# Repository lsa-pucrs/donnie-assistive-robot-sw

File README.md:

<!---
[//]: # incluir travis
[//]: #| Linux                           |
[//]: #|---------------------------------|
[//]: #| [![Build Status][master]][repo] |
[//]: # https://github.com/forexample/package-example/blob/master/CMakeLists.txt

[//]: #[master]: https://travis-ci.org/forexample/package-example.svg?branch=master
[//]: #[repo]: https://travis-ci.org/forexample/package-example
-->

# Donnie Software Stack

Robotics has been used to teach young students the basics of programming. However,
most of the programming environments for kids are high visual, based on grab and drag blocks.
**Blind students or students with some visual disability cannot use these teaching resources**.

Donnie project proposes an inclusive robotic programming environment where all students
(with or without visual disabilities) can use.

Donnie comes with two usage options: simulated robot and physical robot. It is recommended to start with the simulated since it does not require building the robot. Moreover, currently the physical robot is functional, but it is still under test.

Currently Donnie is working fine in Linux Operating System, it is not working on Windows Operating Sytem neither in MacOS.

Contents
--------

1. [Features](#features)
2. [Getting Started with the Simulated Donnie Robot](#getting-started-with-the-simulated-donnie-robot)
3. [Building Your Donnie Robot](#building-your-donnie-robot)
4. [Contributors](#contributors)
5. [Contributing](#contributing)
6. [Support](#support)
7. [Papers](#papers)

# Features
---------------

* Robot programming environment for young students with or without visual impairment;
* Assistive programming language called GoDonnie. GoDonnie is TTS and screen reader friendly;
* Integration with a Arduino-based robot with Player robotic middleware;
* Extension of Stage simulator to generate sound clues while the robot is moving;
* Software developed for the simulated robot is compatible with the real Donnie robot;

# Getting Started with the Simulated Donnie Robot
---------------

<!---
TODO colocar um link do Donnie no youtube

-->

 <!--The simulation is recommended if you want to known about Donnie but you dont have the required resources to build your own Donnie robot.-->

 <!--Download this [VM](http://www.osboxes.org/linux-mint/), select the Linux Mint 17.3 'Rosa', and selected the [Mate](https://drive.google.com/file/d/0B_HAFnYs6Ur-NGFCZWNFV2dBN2M/view?usp=sharing) version. Finally, follow the instructions to install Donnie package.
 -->

## Operating System Requirement
 --------
 1. Currently this project requires Ubuntu 16.04.
 [**Ubuntu 16.04**](http://releases.ubuntu.com/16.04/) (Xenial Xerus) is the recommended OS distribution.
 For older computers or VMs, [Lubuntu 16.04](http://cdimage.ubuntu.com/lubuntu/releases/16.04/release/) or [Ubuntu Mate 16.04](https://ubuntu-mate.org/trusty/) are recommended.
 
<!-- * It is recommended to update your packages before the instalation:
> sudo apt-get update
* To install, you can double-click it or execute:
> sudo dpkg -i donnie-player-stage_0.1_amd64.deb
* In case of missing dependencies, try: 
> sudo apt-get -f install
* To unistall:
> sudo dpkg -r donnie-player-stage -->

## Compile and Install Donnie Software on a Desktop Computer

1.Open a terminal, and execute the following commands:

	mkdir ~/donnie; cd ~/donnie
	git clone --recurse-submodules -b devel https://github.com/lsa-pucrs/donnie-assistive-robot-sw.git
	cd donnie-assistive-robot-sw
	chmod +x ./install.sh
	export DONNIE_PATH=/opt/donnie 
	./install.sh
	
2. After the execution of the last command  above, if the installation finished successfully you are ready to go! 
note:The last command above, in general, requires a lot of time to finish.

### Configuring Donnie

The installation scripts make a standard instalation we believe is the most appropriated for the average user.
However, advanced parameters can be set if the user has experience with the appropriate tools.

The build system is based on CMake, so it is required to have some experience with Linux, Make, and CMake.
Every part of Donnie Software Stack is also based on CMake. These are the software parts that can be customized:

- raspicam driver
- [Player](https://github.com/playerproject/player)
- [Stage](https://github.com/rtv/Stage)
- Donnie Software

each of these packages have their one sets of parameters.

Developers interested in customization might want to read the following files:

- [install.sh](install.sh). For desktop setup procedure.
- [install/setup.sh](install/setup.sh)
- [install-rpi.sh](install-rpi.sh). For embedded computer setup procedure.
- [install/setup-rpi.sh](install/setup-rpi.sh)
- and all the CMakeLists.txt files

### Learning Player and Stage

Donnie is based on Player/Stage robotic middlware and simulator. It is higly 
recommended for Donnie developers to understand Player/Stage to add more features,
create new elaborated scenarios, etc. The official documents are [Player](https://playerproject.github.io/), [Player wiki](https://github.com/playerproject/player/wiki) and [Stage](http://rtv.github.io/Stage/).
However, the best documentation is the [Player/Stage tutorial](http://player-stage-manual.readthedocs.io). 

### Parameter for Donnie Software

The following list explains Donnie's main compilation parameters:

	BUILD_DOCS           OFF              Generate Donnie's documents.
	BUILD_DOXYGEN        ON               This is the default document in HTML, meant only for developers.
	BUILD_DOXYGEN_PDF    OFF              The same document before, but in PDF.
	BUILD_EXAMPLES       OFF              Build the examples for each part of Donnie.
	BUILD_MANUAL         OFF              Build the manuals: software manual, hardware manual, user manual.
	CMAKE_BUILD_TYPE     Release | Debug  Debug mode is for developers only !
	DOC_LANGUAGE         en | pt-br | es  The language used to build documents and the GoDonnie interpreter. Future work !

# Building Your Donnie Robot
---------------

To build your own Donnie robot, please refer to the following repositories (github login and read acess required!):

* [Donnie eletronics](https://github.com/lsa-pucrs/donnie-assistive-robot-hw)
* [Donnie 3D printing](https://github.com/lsa-pucrs/donnie-assistive-robot-3d)

## Install Donnie Software on a Donnie's Embedded Computer (Raspberry Pi)

  Once the eletronics and the 3D printing were done, one must load the operating system and Donnie's software into SD Card.

### Install the Donnie Image into the SD Card

  The easiest way to setup Donnie's embedded computer is to use the pre-built image. Please follow these steps to burn the SD card:

  	wget xxxxxxxxx.img
	continue ...

### Compile, Configure the OS, and Install the Donnie Image into the SD Card

  This option is for programmers with experience with Raspberry Pi.

 [**Raspbian 8.0**](https://www.raspberrypi.org/downloads/raspbian/) (Jessie) is the recommended OS distribution for Donnie robot.
 Logon the Donnie's embedded computer, open a terminal, download this script, and execute it

	mkdir ~/donnie; cd ~/donnie
	wget https://github.com/lsa-pucrs/donnie-assistive-robot-sw/raw/devel/install-rpi.sh
	chmod +x ./install-rpi.sh 
	export DONNIE_PATH=/opt/donnie
	./install-rpi.sh

 Experienced programmers can configure the same paramerters presented before for the Raspberry Pi.

# Contributors
------------

We thank the following people for contributing to **Donnie**:

* [Alexandre Amory](https://github.com/amamory): Hardware design, Embedded software, software stack, robotic middleware, build system
* [Augusto Bergamin](https://github.com/AugustoPB): Hardware design, Arduino programming, Embedded software, GoDonnie parser
* [Camila Kolling](https://github.com/camilakolling): assistive evaluation, testing, testing with blind users
* [Daniel Einloft](https://github.com/DanielEinlof): odometry, blobfinder, raspicam driver
* [Guilherme Marques](https://github.com/marquesgh2m): Hardware design, Arduino programming, Embedded software, software stack, robotic middleware
* [Henry Nunes](https://github.com/HenryNunes): assistive evaluation, testing, testing with blind users
* [Isabel Manssour](https://github.com/isabelhm): Computer vision
* [Juliana Damasio](https://github.com/julianadamasio): assistive evaluation, testing, testing with blind users
* [Joice Marek](https://github.com/joiceMarek): visual odometry, raspicam driver
* [Marcia Campos](https://github.com/marciabcampos): assistive evaluation, testing, testing with blind users
* [Renan Maidana](https://github.com/rgmaidana): Hardware design, Embedded software, Arduino programming, software stack, robotic middleware, build system

# Contributing
------------

Donnie project has a small core team and it relies on external collaboration to continue developing this assistive system.
This is a list of itens the core team wish to have some help:

* Translattion to other languages. Both the GoDonnie commands and Donnie's documents have to be translated. In the near future we wish to support en, pt-br, es;
* More documentation and tutorials. Currently we are building English docs;
* More examples using GoDonnie language;
* Porting to Windows. It currently works only on Linux, however, Windows has great assitive tools such as NVDA;
* Web-based frontend. so it can be used without much installation and setup;
* Integrate more assistive tools for blind users such as ORCA, NVDA, among others;
* Feature requests and testing. Please use the [Issue](https://github.com/lsa-pucrs/donnie-assistive-robot-sw/issues) system to request new features and to report bugs;

# Demonstration
------------
This [video](https://www.youtube.com/watch?v=BRXAqvGPGmU) demonstrates the functionality of Donnie Robot and Donnie simulation. In this task the robot is asked to move forward until hitting a wall, then it must turn to the right.

# Support
------------

Please use the github [Issue](https://github.com/lsa-pucrs/donnie-assistive-robot-sw/issues) for support.

# Papers
------------

If you are using Donnie on your research projects, please cite our papers:

	@inproceedings{oliveira2017teaching,
	  title={Teaching Robot Programming Activities for Visually Impaired Students: A Systematic Review},
	  author={Oliveira, Juliana Damasio and de Borba Campos, M{\'a}rcia and de Morais Amory, Alexandre and Manssour, Isabel Harb},
	  booktitle={International Conference on Universal Access in Human-Computer Interaction},
	  pages={155--167},
	  year={2017},
	  organization={Springer}
	}

	@inproceedings{guilherme2017donnie,
	  title={Donnie Robot: Towards an Accessible And Educational Robot for Visually Impaired People},
	  author={Guilherme H. M. Marques, Daniel C. Einloft, Augusto C. P. Bergamin, Joice A. Marek, Renan G. Maidana Marcia B. Campos, Isabel H. Manssour, Alexandre M. Amory},
	  booktitle={Latin American Robotics Symposium (LARS)},
	  year={2017}
	}

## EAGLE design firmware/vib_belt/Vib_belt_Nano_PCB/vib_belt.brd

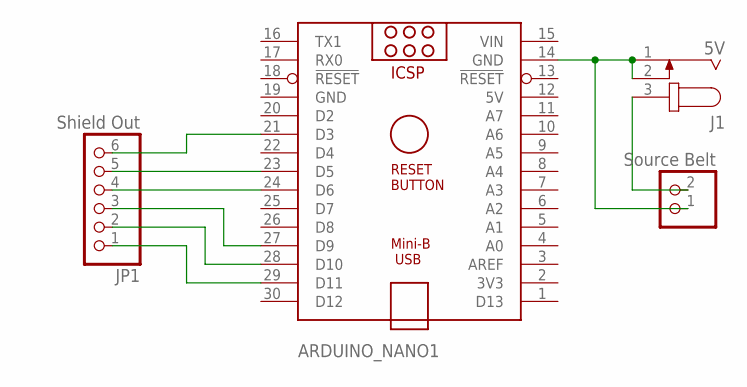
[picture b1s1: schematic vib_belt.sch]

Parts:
ARDUINO_NANO1: ARDUINO_NANO
J1: 5V; SPC4077
JP1: Shield Out; 1X06/90
JP2: Source Belt; 1X02/90

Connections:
5V: ARDUINO_NANO1.12 (5V)
GND: ARDUINO_NANO1.19 (GND)
unnamed: ARDUINO_NANO1.14 (GND), J1.1, J1.2, JP2.1
unnamed: J1.3, JP2.2
unnamed: ARDUINO_NANO1.29 (D11), JP1.1
unnamed: ARDUINO_NANO1.28 (D10), JP1.2
unnamed: ARDUINO_NANO1.27 (D9), JP1.3
unnamed: ARDUINO_NANO1.24 (D6), JP1.4
unnamed: ARDUINO_NANO1.23 (D5), JP1.5
unnamed: ARDUINO_NANO1.21 (D3), JP1.6
VIN: ARDUINO_NANO1.15 (VIN)

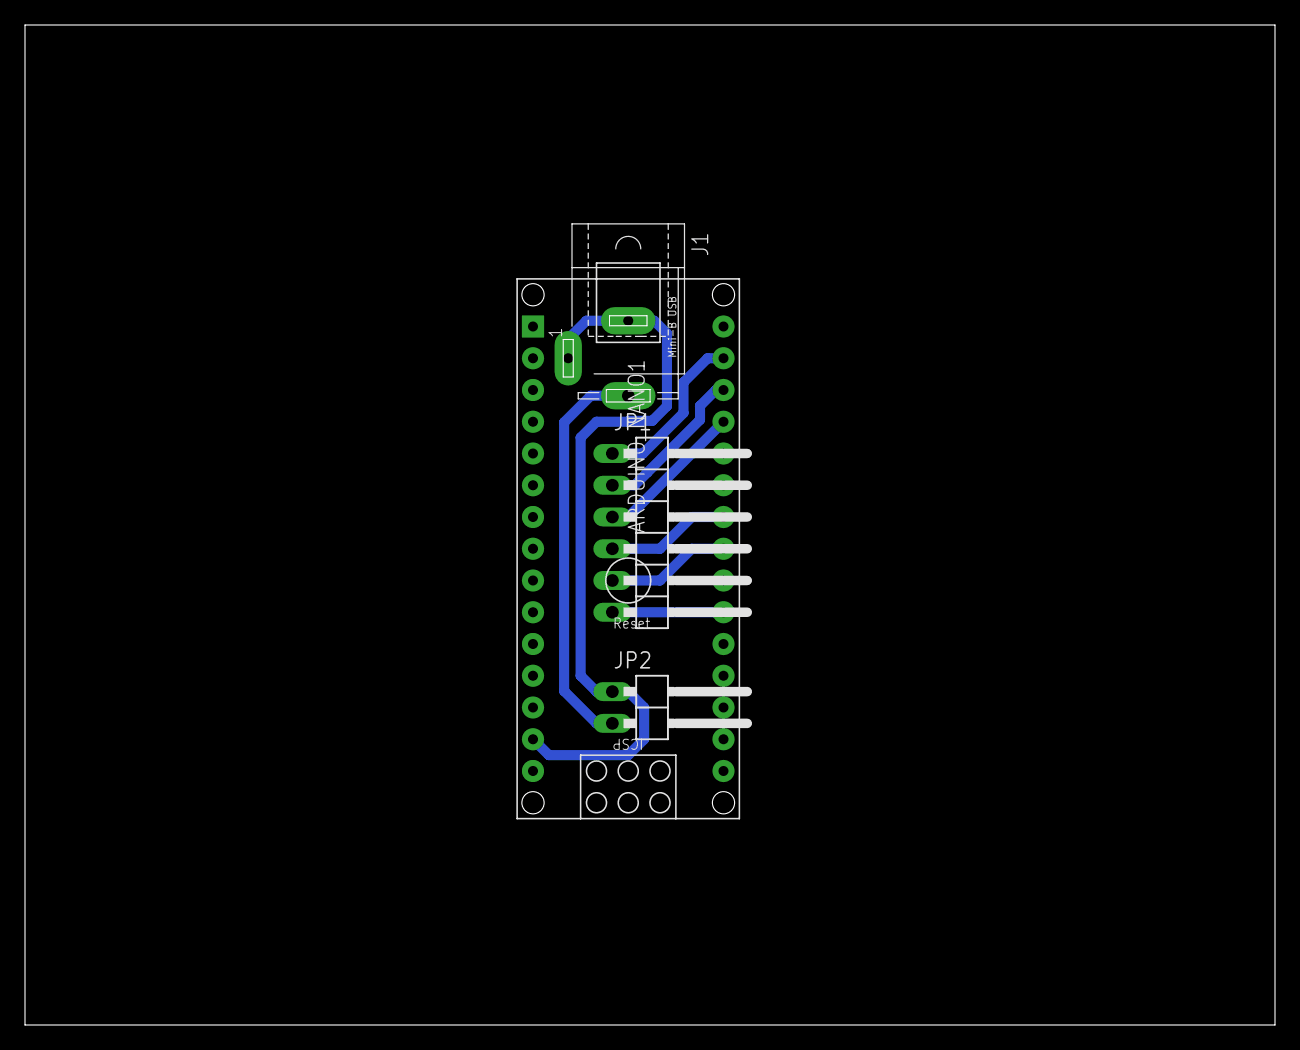
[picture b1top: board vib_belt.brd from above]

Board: 2 copper layers, 100.0 x 80.0 mm, 4 parts (0 on the bottom side), 8 nets.

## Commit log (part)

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2017-05-27 readme travis
2017-05-27 including travis.yml
2017-05-27 travis
2017-05-27 travis set donnie_path
2017-05-27 replace oracle's java by openjdk
2017-05-27 install
2017-05-29 setup script for debian package
2017-05-29 install steps
2017-05-31 feedback com áudio para comando 'som ligado/desligado'. BugFix #103
2017-06-01 Resolvido bug da cor
2017-06-01 correcao no driver para se comunicar com Godonnie terminal
2017-06-06 fixed Goto command from Godonnie
2017-06-06 fixed the bug in which the robot did not stop spinning while speaching
2017-06-07 added goto to driver for rotation of the head
2017-06-07 fixed head rotation with espiar command
2017-06-08 tutorial de criação de pacotes deb
2017-06-08 moving docs
2017-06-08 fix to work on 16.04
2017-06-08 alterado para funcionar também no 16.04
2017-06-09 readme typos
2017-06-13 prints removed
2017-06-13 cleaning the motors.h code
2017-06-25 starting wiiki pages
2017-06-25 add player-stage manual submodule
2017-06-25 including links to download the VM and links to the external Player-Stage docs
2017-06-25 excludin gsubmodule with Player-Stage docs
2017-06-26 create mkdocs.yml
    initial structure for Donnie manual based on Markdown
2017-07-12 including raspberry pi configuration tutorial
2017-07-17 removing unnecessary depedency checks
2017-07-17 prearing donnie for the git-based player version. replaced sound interface by playsound. few test source code files renamed
2017-07-18 adapting gtts and soxplayer
2017-07-19 correcting gtts and soxplayer drivers. donnie is working with the newer player version
2017-07-28 including libeigen3-dev
    dependency required by Player's EKF driver
2017-11-05 papers
2017-11-09 video
2018-01-15 fix cmake to read the CMAKE_MODULE_PATH env variable
2018-01-16 fixing cmake_module_path and pkg path, removinig raspicam from desktop compilation, disabling docs compilation for donnie
2018-01-16 commenting head sonar proxy. error to connect to it. in the future this must be investigated to enable it again
2018-01-17 initial sphinx doc integrated with ReadTheDocs
2018-01-17 remove video
2018-01-17 inital template to develop the vibrating belt driver
2018-01-17 removing SET CMAKE_MODULE_PATH from CMakefileLists
2018-01-17 fixing docs/conf.py for running sphinx and rtd
2018-01-18 Disabled verbose output from install.sh
2018-01-18 Added environmental variable instruction for source compilation in README.md
2018-01-18 fix conf.py
2018-03-05 added initial text, MIT license and papers
2018-03-07 added export path to install.sh to avoid setting it beforehand
2018-03-07 added environmental variable and function variants for different languages (en_US and pt_BR)
2018-03-07 changed logic for language ifs
2018-03-07 removed export DONNIE_PATH
2018-03-07 syntax error fix
2018-03-07 added dependency for boost library in CMakeLists.txt
2018-03-07 added boost dependency installation in install.sh
2018-03-07 added boost_locale library to alerts.h
2018-03-07 added support for boost_locale and changed log messages to auto-translate
2018-03-07 linked boost libraries in alerts cmake
2018-03-07 generated translation files in en_US and pt_BR
2018-03-07 added readme to localization folder
2018-03-07 added contributors to readme
2018-03-07 changed dependency from libboost-all-dev to libboost-locale-dev
2018-03-07 fixed error in previous commit, uncommented player and stage instalation commands
2018-03-07 changed link to ref only boost_locale library
2018-03-07 added boost requirement to godonnie cmakelists
2018-03-07 added boost requirement to donnie cmakelists
2018-03-07 removed LINK_PUBLIC flag
2018-03-07 added folders downloaded by running install.sh in the cloned repo
2018-03-08 added requirement and linking for boost_locale library
2018-03-09 added locale-gen for generation of supported languages
2018-03-09 added support for en_US language, selectable through DONNIE_LANG env variable
2018-03-09 localization of Compiler code, from godonnie interpreter
2018-03-09 localization for DonnieClient code, from godonnie interpreter
2018-03-09 added missing english files for Compiler localization
2018-03-09 localization for DonnieMemory code, from godonnie interpreter
2018-03-09 localization of Exception code, from godonnie interpreter
2018-03-09 localization of GoDonnie code, from godonnie interpreter
2018-03-09 localization of Historic code, from godonnie interpreter
2018-03-10 added support for en_US in exception messages
2018-03-10 fixed bugs in localization
2018-03-10 added todo list in README
2018-03-13 updated docs up to robot construction
2018-03-13 fixed bugs in GoDonnie.g, Compiler.cpp and updated the translation files with new linenumbers
2018-03-13 removed GoDonnie_old.g, GoDonnie_en_US.g and GoDonnie_pt_BR.g
2018-03-13 readded alerts folder which disappeared for some reason
2018-03-13 fixed bugs in GoDonnie.cpp and Historic.cpp
2018-03-16 changed loc folder from root to resources
2018-03-16 Added instructions for install of localization files to /opt/donnie
2018-03-16 removed loc folder from root
2018-03-16 changed source files to match new localization file location
2018-05-29 testing
2018-06-06 including dir for the vib belt
2018-06-06 All firmware using clang-format with GOOGLE style
2018-06-06 All utils using clang-format with GOOGLE style
2018-06-06 All godonnie using clang-format with GOOGLE style
2018-06-06 All client/alerts using clang-format with GOOGLE style
2018-06-06 All client/test using clang-format with GOOGLE style
2018-06-13 change doc title, add initial warning, and link to the user manual
2018-06-13 change link
2018-06-18 vib_belt
    Including the vib_belt code
2018-06-28 initial version of belt on-off command
2018-06-28 cleaning up vib_belt client. vib_belt driver removed
2018-06-30 updating the cmake for visual_odometry. this cmake still need some modifications. left for future work
2018-06-30 included log flag for godonnie. correcting cmakelist using locale. fixing few translation errors.
2018-06-30 updating travis file with locale depedency
2018-06-30 issue #92 closed. now godonnie parameters are case insensitive
2018-07-01 Fixed bug regarding issue #112, where the sound on/off did not work
2018-07-01 Fixed bug related to issue #112, corrected belt command conditional
2018-07-01 Fixed bug related to issue #112, added belt on/off command in en_US
2018-07-01 Updated localization files for the belt command
2018-07-01 Added instructions to updating localization files
2018-07-13 Fixed apt-get update command
2018-07-13 Alterei as ocorrencias da versão Ubuntu 14.04 para 16.04
2018-08-08 fixed color and scan bug
2018-08-24 vib belt in c++. not working yet
2018-09-10 reserved Words implementation
2018-10-11 closing issue #110 related to donnie closing during startup
2018-10-11 sound bug fix
2018-10-12 initial version of driver floorplan_description
2018-10-12 replacing ranger interface by log interface in the floorplan_description driver
2018-10-12 initial vib_belt is reading from sensors. next step is to test the serial comm with the actual belt
2018-10-12 2nd version of the vib-belt driver
2018-10-12 initial version of command vibrate. command belt on-off is working. godonnie is crashing if two commands a sent
2018-10-13 including ranger2vib
2018-10-14 giving up from the ranger2vib driver. using a client for the same purpose. vib_belt driver initially ok. needs more testing
2018-10-14 renaming client to ranger2vib
2018-10-14 adding two donnies in a single scenario
2018-10-15 new maze scenarios
2018-10-15 house scenario
2018-10-16 vib_belt working with serial comm. ranger2vib working. fixing cmake bugs for test clients
2018-10-18 fixing bug #119 when godonnie executec a file. issue was related to wrong getopt argument
2018-10-22 reserved words fix
2018-10-24 including initial yaml files to describe a scenario
2018-10-24 Donnie retorna se a variavel é valida ou não
2018-10-24 including vibration intensity in to the grammar. not tested yet
2018-10-24 including floor_desc client. including yaml-cpp
2018-10-25 improving yaml reader for floor_desc. still not ready
2018-10-25 reading keys for floorplan desrpition
2018-10-26 key binds are working for floor_desc
2018-10-29 consistency checking for yaml reading
2018-10-29 start iterator navigation in the yaml nodes
2018-11-05 'cinto' added to reservedWords
2018-11-09 removing vib belt from cfg
2018-12-04 fix translations. issue #122
2018-12-14 Translation
2019-03-06 Corrected criar command
2019-03-20 Updated Arduino pins based on the new board
2019-03-20 Added new Arduino Code, Eagle Electric Schematic and Fritzing files
2019-03-21 Updated new Arduino software behaviour for errors
2019-03-21 Added the required libraries for both EAGLE projects
2019-03-28 rpi install script updated to raspbian 8.0
2019-04-10 Integrated GoDonnie with real robot;
2019-04-11 added text in the 'Building your Donnie Robot' part
2019-04-11 minor
2019-04-17 minor change
2019-04-22 added content in How to Create a New Environment
2019-04-22 testing docs
2019-04-22 testing with anorther project
2019-04-24 fixing install/setup-rpi.sh.in, donnie firmware
2019-04-24 fixing install-rpi.sh, driver gtt, soxplayer, donnie test
2019-04-24 updating install-rpi.sh install.sh
2019-04-24 removing boost locale depedency for the donnie driver
2019-04-24 removed files from building folder
2019-04-26 fixing gtts for rasp and migrating opencv to version 3
2019-05-03 Fixing GoDonnie's Scan and Color commands.
2019-05-06 Fixing robot rotation with GoDonnie
2019-05-08 Fixing issue where Donnie kept turning.
2019-05-12 reorganizing donnie's dependencies by using sigt submodules. this will simplify the install.sh script, specially because we have to compile openCV 3.1
2019-05-12 adding prebuilt opencv 3.2 to the travis file
2019-05-12 fixing travis file
2019-05-12 fixing travis
2019-05-12 fixing travis w player opencv
2019-05-12 including prebuilt opencv 3.2 for ubuntu 14.04 and 16.04
2019-05-23 Fixing GoDonnie's belt functions and Rangers sequence.
2019-05-24 Fixing 2 inverted variables names.
2019-05-24 fixing instal script for raspbian strech
2019-05-24 updating rpi install for raspbian strech
2019-05-28 Adding Raspberry configuration to install-rpi.sh
2019-05-30 Updating Raspberry install
2019-06-19 Fixing Donnie Install on Ubuntu
2019-07-02 Adjusting Donnie installation on PC
2019-07-19 Setting up Player on Raspberry startup
2019-10-24 EN_us forced
    Line 172
    From:
    string langurl = "&tl=" + lang;
    To:
    string langurl = "&tl=" + "EN_us";
2019-10-24 EN_us forced
    Line 181
    From:
    string langurl = "&tl=" + lang;
    To:
    string langurl = "&tl=" + "EN_us";
